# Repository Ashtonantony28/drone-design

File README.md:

# drone-design: NF-3D

A complete small quadcopter designed entirely in code, in a cloud container. It is built around the
[neuroflight-fc](https://github.com/Ashtonantony28/neuroflight-fc) learned flight controller and
flight-tested in that project's simulator.

- **Electronics:** the neuroflight-fc flight controller written in **Zener** with Diode's
  [`pcb`](https://github.com/diodeinc/pcb) toolchain (the E-CAD used in the Fable 5.2 electronics demo),
  laid out and DRC-checked in **KiCad 10**.
- **Mechanics:** a parametric frame in **build123d** (Python CAD), with mass, clearance, FEA and
  manufacturing exports.
- **Validation:** propulsion model, structural FEA and flight simulation, each with pass/fail gates.

## Gallery

**NF-3D Lite** (`lite/`, the low-cost brushed micro build): the 222-part detailed model that `lite/audit.py`
checks (0 overlaps, 0 floating parts), props turning in their real directions.

| Flight board as assembled | Carbon NF-3D v1 |
|:---:|:---:|
|  |  |

**Vision autonomy (simulation).** The AprilTag search, follow, approach and land behaviours flown closed-loop:
neuroflight-fc simulator, synthetic OV2640 frames, the laptop's real detector and controller, 150 ms link latency.
Nothing here has flown on hardware yet. Full 35 s clip with both episodes: [vision-replay.mp4](docs/media/vision-replay.mp4).

<sub>Regenerate: `xvfb-run -a python -m lite.turntable` (turntable, hero still, board still) and
`python -m lite.vision_replay` (needs `../neuroflight-fc`, torch, opencv).</sub>

## The vehicle

| | |
|---|---|
| Class | 3" ducted quad, 4S, sub-250 g |
| Motor spacing | 100 mm square (141 mm diagonal), widened from neuroflight's 92 mm so the 30.5 mm FC stack clears the ducts |
| All-up weight | **238.8 g** (CAD mass model, requirement ≤ 249 g) |
| Thrust/weight | **5.9** nominal, 4.3 in the pessimistic corner (requirement ≥ 3) |
| Hover | 28 % throttle, **8.8 min** hover (5.3 min pessimistic; requirement ≥ 4) |
| Frame | 3.0 mm carbon unibody with closed ring perimeter, PA12-CF printed ducts, TPU feet |
| FC | STM32H743, ICM-42688-P + BMI270, DPS310, 1 Gbit NAND, 36x36 mm 4-layer, 143 parts |

Every number comes from `spec/vehicle.yaml`. It is the single source that the CAD, mass model,
propulsion model, FEA and flight simulator all read.

## Verify

```
make verify          # mech -> propulsion -> fea -> flight (needs ../neuroflight-fc, torch)
cd ecad && python -m pytest check_design.py check_layout.py -q
docker run --rm -v $PWD:$PWD -w $PWD/ecad kicad/kicad:10.0.8 \
  kicad-cli pcb drc --severity-all boards/nf_fc/layout/nf_fc/nf_fc.kicad_pcb
```

| Check | Result |
|---|---|
| `mech.checks`: interference, clearances ≥ 1 mm, prop tip gap 1.0 mm, prop inside duct, feet are the lowest point, CoG offset | PASS |
| `prop.propulsion`, nominal and pessimistic corners (ct −15 %, cp +20 %, mass +5 %) | PASS |
| `mech.fea`: 20 g single-foot crash | SF **1.53** (≥ 1.5) at 1.6 mm mesh |
| `mech.fea`: full thrust | SF 31 |
| `mech.fea`: first frame mode | 213-221 Hz, 21-32 % away from hover rotor speed (≥ 20 %) |
| `flight.fly`: PID fallback on NF-3D vs the original neuroflight vehicle, 256 randomized vehicles per scenario | PASS (within 3 points in both corners) |
| `flight.fly`: v3 policy with thrust calibration (`v3cal`), same comparison (advisory) | within 3 points in both corners |
| `pcb build` (Zener) | 143 components, no errors or warnings |
| `ecad/check_design.py` (pin map, decoupling, rails, BOM vs neuroflight-fc) | 9 passed |
| `ecad/check_layout.py` (IMU spacing, DShot length, holes, decoupling, GND plane, USB pair, QSPI match, power widths and pours, track/space margin, silkscreen) | 17 passed |
| KiCad 10 DRC | **0 errors, 0 unconnected, 0 warnings** (the two library-footprint comparison checks, 120 warnings that depend on the installed footprint libraries, are set to ignore in `layout/place.py`) |

The frame took five FEA iterations to pass: crash safety factor 0.5 → 0.95 → 1.27 → 1.45 → 1.7, and
first mode 118 → 221 Hz. The changes were ring bridges, a 3 mm plate, wider arms, a bigger centre body
and filleted arm roots.

## Findings and open items

1. **The neural policy flies NF-3D after a thrust calibration, with no retraining.** neuroflight's
   `hover_ctbr_v3` used as-is holds up on the nominal NF-3D (99.2/85.9/95.3 % hover/tilt/throw). On the
   weak-motor corner it drops to 50/34/54 %, because its thrust command is in the reference vehicle's
   units and the policy has no integral action. `flight/fly.py` `CollectiveScaled` reads the command as
   mass-normalized and rescales it to this airframe:
   `a0' = (a0+1)·s − 1`, with `s = (T_max,ref · m) / (T_max · m_ref)`. That is what a hover-thrust
   estimator does on PX4/ArduPilot. With it, v3 scores **100/89.5/98.0 %** nominal and
   **100/90.2/98.0 %** pessimistic, against 100/90.6/97.3 % on the reference vehicle, so both corners
   are within the 3-point margin. Fine-tuning was tried first and doesn't work: every run lost v3's
   cm-level hover, including on the reference vehicle. `flight/retrain.py` records what was ruled out.
   Firmware follow-up for neuroflight-fc: apply `s` (or a learned hover thrust) between the policy
   output and the mixer.
2. **PCB before fab:** the layout items are done and asserted in `ecad/check_layout.py`
   (`python check_layout.py` prints the numbers). USB D+/D− is one 0.24 mm / 0.155 mm pair on L1
   (90.3 Ω by `ecad/layout/impedance.py`), 20.19 mm per line with 0.000 mm skew for both plug
   orientations (was D+ 53 mm vs D− 21 mm); 12.4 mm of it is coupled, the rest is fan-out at the
   MCU pins and the connector. The six QSPI lines are within 1.79 mm (was 29 mm apart on this
   routing), at the price of length: 53.6–55.4 mm each, because the longest line sets the target.
   VBAT, 5V and VBUS tracks are 0.25–0.5 mm (0.25 mm only in necks: 6 of 38 mm, 16 of 101 mm,
   2 of 28 mm) with L4 pours at the buck input and output; 3V3_D is the L3 pour. Silkscreen and
   the dangling via are clean. Still open: 342 mm of 1867 mm of track (18 %) stays 0.1 mm wide
   and 206 mm (11 %) has 0.1 mm space, in the MCU and FPGA escapes; 5V, VBUS and VBAT still have
   0.3–0.5 mm stretches on the 17.5 µm L3 (23, 9 and 9 mm) that should move to the outer layers;
   and the 90 Ω figure is a calculation, not a fab-controlled impedance. The router is this
   repo's own maze router (`ecad/layout/autoroute.py`); another seed or placement change can
   leave a net open, so re-run `layout/run.sh all` and the checks after any edit.
3. **Datasheet VERIFY items:** DPS310 / W25N01GV pinouts, LMR36015 variant and land pattern, IMU
   LGA-14 land patterns, crystal load capacitors, and the J2 pinout against the ESC you buy. All are
   marked `VERIFY` in `ecad/`.
4. **Propulsion numbers are estimates** until the M3 thrust stand; the pessimistic corner covers
   them. The arm mode is 21 % from the nominal hover rotor speed. Re-check once real hover rpm is known.

## Layout

```
spec/vehicle.yaml   single source of truth (geometry, parts, materials, motor/prop, requirements)
mech/               build123d frame, checks, FEA (gmsh + scikit-fem), exports -> out/cad/
prop/               battery-ESC-motor-prop model
flight/             flight validation and policy fine-tune in the neuroflight-fc simulator
ecad/               Zener FC design, layout scripts, KiCad board, checks, fab outputs (gerbers, PnP, STEP)
out/                generated reports, CAD exports, vehicle parameter sets
```

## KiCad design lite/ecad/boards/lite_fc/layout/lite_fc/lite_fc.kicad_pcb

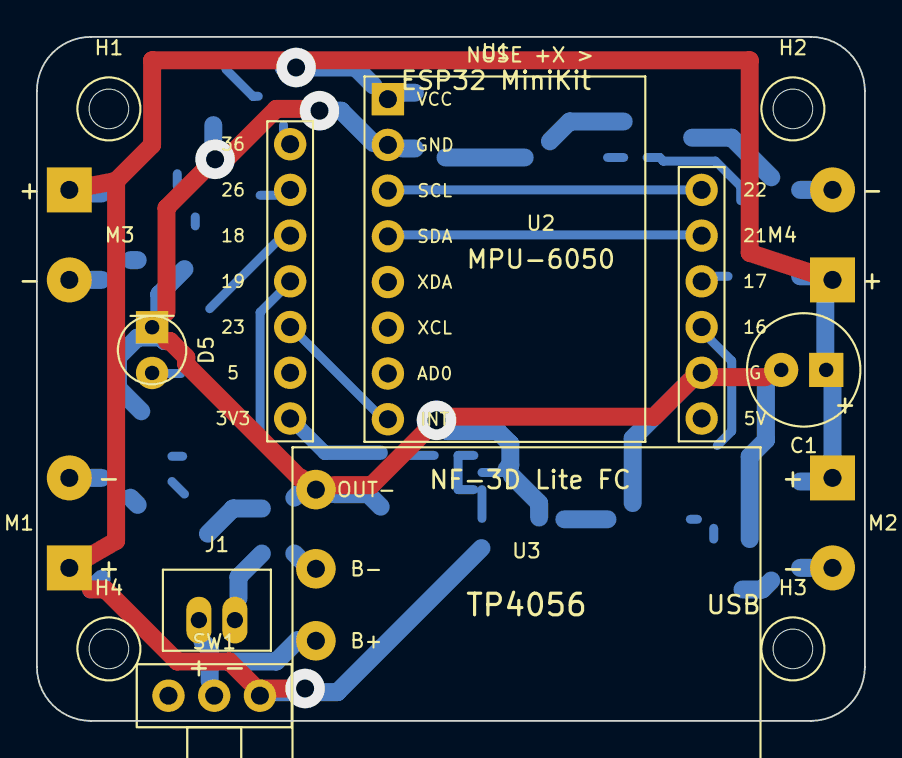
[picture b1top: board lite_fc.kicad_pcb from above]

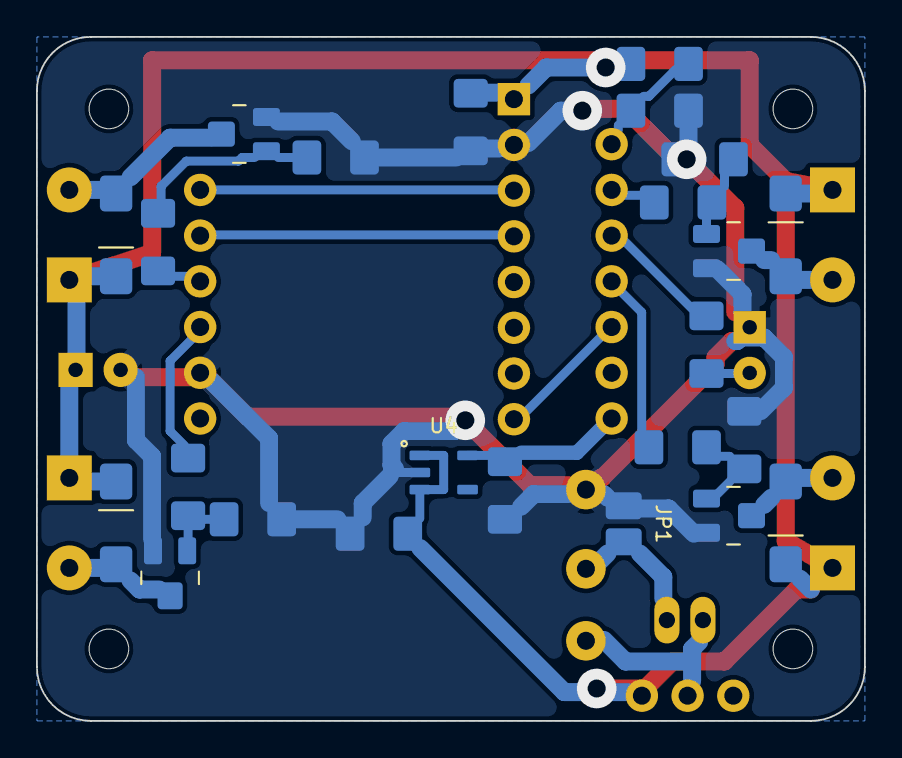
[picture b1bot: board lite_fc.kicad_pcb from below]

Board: 2 copper layers, 46.0 x 38.0 mm, 39 parts (24 on the bottom side), 23 nets.

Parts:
C1: 470uF 6.3V electrolytic D6.3; CP_Radial_D6.3_P2.5_Mill
C2, C3: 10uF 10V X5R 1206; C_1206_Mill
C4: 100nF 50V X7R 1206; C_1206_Mill
D1, D2, D3, D4: B5819W Schottky 1A 40V SOD-123; D_SMA_SOD-123_Mill
D5: 3mm LED; LED_D3.0_Mill
H1, H2, H3, H4: MountingHole; MountingHole_2.2mm_M2_Mill
J1: JST PH2.0 2-pin vertical (battery); JST_PH_B2B_Vertical_Mill
JP1: protection bypass (open); SolderJumper_2_Open_Mill
M1, M2, M3, M4: 8520 brushed motor pads; MotorPads_2_P5.0_Mill
Q1, Q2, Q3, Q4: AO3400A; SOT-23_Mill
R1, R2, R3, R4: 100R 1% 1206; R_1206_Mill
R5, R6, R7, R8: 10k 1% 1206; R_1206_Mill
R9: 100k 1% 1206; R_1206_Mill
R10: 47k 1% 1206; R_1206_Mill
R11: 330R 1% 1206; R_1206_Mill
SW1: SS-12D00 SPDT slide switch; SW_SPDT_SS12D00_Mill
U1: ESP32 MiniKit (MH-ET LIVE D1 mini, ESP32-WROOM-32); ESP32_MiniKit_InnerRows_Mill
U2: GY-521 MPU-6050; GY521_MPU6050_Mill
U3: TP4056 + DW01 charger module (03962A); TP4056_Protected_Module_Mill
U4: ME6211C33M5G 3.3V 500mA LDO; SOT-23-5_Mill

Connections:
3V3: C3.1, U1.L8, U4.5
BAT_N: J1.1, JP1.2, U3.2
BAT_P: J1.2, SW1.2, U3.1
GND: C1.2, C2.2, C3.2, C4.2, D5.1, JP1.1, Q1.2, Q2.2, Q3.2, Q4.2, R5.2, R6.2, R7.2, R8.2, R10.2, U1.R7, U2.2, U3.3, U4.2
I2C_SCL: U1.R3, U2.3
I2C_SDA: U1.R4, U2.4
IMU_INT: U1.L6, U2.8
LED: R11.1, U1.L4
LED_A: D5.2, R11.2
M1_G: Q1.1, R1.2, R5.1
M1_N: D1.2, M1.2, Q1.3
M1_PWM: R1.1, U1.L5
M2_G: Q2.1, R2.2, R6.1
M2_N: D2.2, M2.2, Q2.3
M2_PWM: R2.1, U1.R6
M3_G: Q3.1, R3.2, R7.1
M3_N: D3.2, M3.2, Q3.3
M3_PWM: R3.1, U1.L3
M4_G: Q4.1, R4.2, R8.1
M4_N: D4.2, M4.2, Q4.3
M4_PWM: R4.1, U1.R5
VBAT: C1.1, C2.1, C4.1, D1.1, D2.1, D3.1, D4.1, M1.1, M2.1, M3.1, M4.1, R9.1, SW1.3, U2.1, U4.1, U4.3
VBAT_SENSE: R9.2, R10.1, U1.L2

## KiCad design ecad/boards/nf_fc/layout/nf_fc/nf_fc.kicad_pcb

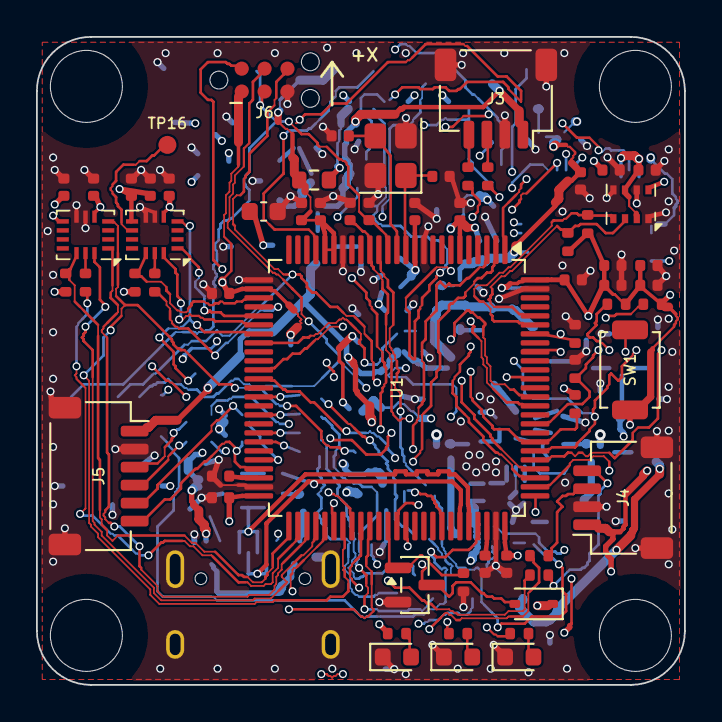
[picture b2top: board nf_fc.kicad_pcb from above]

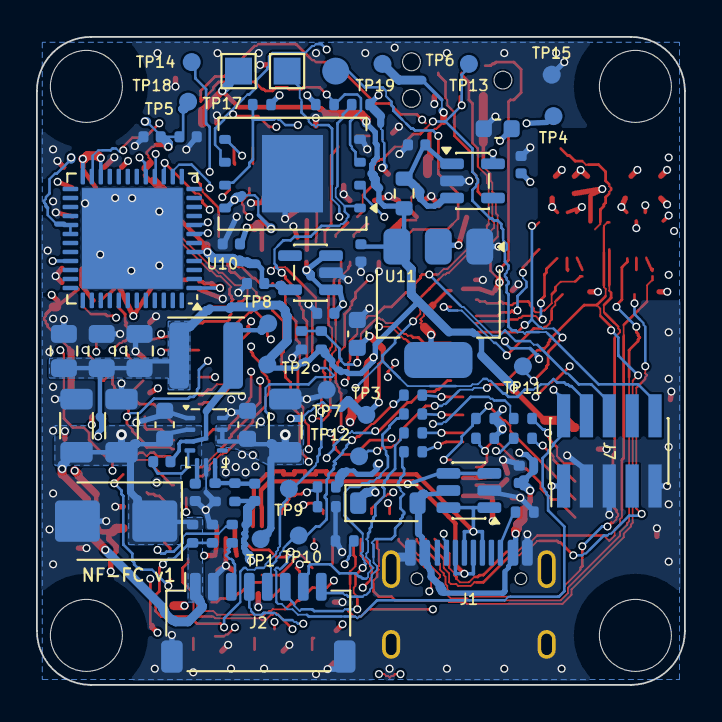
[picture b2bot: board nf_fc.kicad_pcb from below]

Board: 4 copper layers, 36.0 x 36.0 mm, 143 parts (76 on the bottom side), 90 nets.

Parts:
C1, C2, C3, C4, C5, C6, C7, C8, C9, C10, C11, C14, C15, C16, C19, C20, C24, C25, C26, C27, C28, C29, C34, C49: 100nF 16V X7R; C_0402_1005Metric
C12: 10nF 50V X7R; C_0402_1005Metric
C13, C21, C22: 2.2uF 6.3V X5R; C_0402_1005Metric
C17, C18: 12pF 50V C0G; C_0402_1005Metric
C23, C36, C38, C39, C41, C42, C46: 1uF 25V X5R; C_0402_1005Metric
C30, C37, C40: 10uF 10V X5R; C_0603_1608Metric
C31, C32, C33: 22uF 25V X5R; C_0805_2012Metric
C35: 20pF 50V C0G; C_0402_1005Metric
C43, C44, C45: 2.2uF 50V X7R; C_1206_3216Metric
C47, C48: 220nF 100V X7R; C_0603_1608Metric
D1: B5819W; D_SOD-123
D2: 1N4148WS; D_SOD-323
D3: 26V TVS Diode; D_SMB
D4: LED GREEN 2.7–3.2V (3V nom.); LED_0603_1608Metric
D5: LED BLUE 2.7–3.2V (3V nom.); LED_0603_1608Metric
D6: LED RED 2V 10%; LED_0603_1608Metric
FB1, FB2: 600 1A 100MHz; R_0603_1608Metric
H1, H2, H3, H4: MountingHole; MountingHole_4.0mm_M3_Grommet
J1: TYPE-C-31-M-12; USB_C_Receptacle_HRO_TYPE-C-31-M-12
J2: SM08B-SRSS-TB(LF)(SN); JST_SH_SM08B-SRSS-TB_1x08-1MP_P1.00mm_Horizontal
J3, J4: SM04B-SRSS-TB(LF)(SN); JST_SH_SM04B-SRSS-TB_1x04-1MP_P1.00mm_Horizontal
J5: SM06B-SRSS-TB(LF)(SN); JST_SH_SM06B-SRSS-TB_1x06-1MP_P1.00mm_Horizontal
J6: Conn_ARM_SWD_TagConnect_TC2030-NL; Tag-Connect_TC2030-IDC-NL_2x03_P1.27mm_Vertical
J7: FTSH-105-01-F-DV-K; PinHeader_2x05_P1.27mm_Vertical_SMD
L1: 6.8uH; L_Sunlord_SWPA4030S
Q1: AO3400A; SOT-23
R1, R2: 4.7k 1%; R_0402_1005Metric
R3, R6, R9, R10, R15, R16: 100 1%; R_0402_1005Metric
R4, R5: 2.2k 1%; R_0402_1005Metric
R7, R8: 5.1k 1%; R_0402_1005Metric
R11, R12, R13, R14: 33 1%; R_0402_1005Metric
R17, R18, R19, R20, R22, R24, R25, R26, R28, R31, R32, R35, R37, R38: 10k 1%; R_0402_1005Metric
R21, R23: 0; R_0402_1005Metric
R27, R30: 100k 1%; R_0402_1005Metric
R29: 24.9k 1%; R_0402_1005Metric
R33, R34, R39, R40, R41: 1k 1%; R_0402_1005Metric
R36: 20k 1%; R_0402_1005Metric
SW1: TS-1088-AR02016; SW_SPST_TS-1088-xR020
TP1, TP2, TP3, TP4, TP5, TP6, TP7, TP8, TP9, TP10, TP11, TP12, TP13, TP14, TP15, TP16: TestPoint_Small; TestPoint_Pad_D1.0mm
TP17, TP18: TestPoint_Small; TestPoint_Pad_1.5x1.5mm
TP19: TestPoint_Small; TestPoint_Pad_D1.5mm
U1: STM32H743VIT6; LQFP-100_14x14mm_P0.5mm
U2: ICM-42688-P; Bosch_LGA-14_3x2.5mm_P0.5mm
U3: BMI270; Bosch_LGA-14_3x2.5mm_P0.5mm
U4: DPS310XTSA1; Bosch_LGA-8_2x2.5mm_P0.65mm_ClockwisePinNumbering
U5: W25N01GVZEIG; WSON-8-1EP_8x6mm_P1.27mm_EP3.4x4.3mm
U6: LMR36015FBRNXR; Texas_RNX0012C_VQFN-14-11-1EP_2x3mm_P0.5mm_EP0.25x1.825mm
U7: LDL1117S33R; SOT-223-3_TabPin2
U8: LP5907MFX-3.3/NOPB; SOT-23-5
U9: USBLC6-2SC6; SOT-23-6
U10: iCE40UP5K-SG48ITR; QFN-48-1EP_7x7mm_P0.5mm_EP5.6x5.6mm
U11: TLV75512PDBVR; SOT-23-5
Y1: 8MHz; Crystal_SMD_3225-4Pin_3.2x2.5mm

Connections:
1V2_FPGA: C8.1, C9.1, C10.1, C42.1, TP5.1, U10.5, U10.29, U10.30, U11.5
3V3_D: C1.1, C2.1, C4.1, C5.1, C6.1, C7.1, C11.1, C20.1, C25.1, C26.1, C27.1, C28.1, C29.1, C30.1, C37.1, C41.1, FB2.1, J6.1, J7.1, R1.2, R2.2, R4.2, R5.2, R17.2, R18.2, R19.2, R25.2, R26.2, R28.2, R39.1, SW1.1, TP3.1, U1.6, U1.11, U1.27, U1.50, U1.75, U1.100, U4.2, U4.6, U4.8, U5.8, U7.2, U10.1, U10.22, U10.24, U10.33, U11.1, U11.3
3V3_IMU: C12.1, C13.1, C14.1, C15.1, C16.1, C39.1, C40.1, R20.2, R22.2, TP4.1, U2.5, U2.8, U3.5, U3.8, U8.5
5V: C31.1, C32.1, C33.1, C35.1, C36.1, D1.1, D2.1, FB1.1, J3.1, J4.1, J5.1, L1.2, R30.1, R32.1, TP2.1, TP18.1, U7.3
5V_SENSE: R31.1, R32.2, U1.33
AUX_RX: R3.1, U1.64
AUX_SCL: J5.5, R4.1, U1.46
AUX_SDA: J5.6, R5.1, U1.47
AUX_TX: R6.1, U1.63
BARO_SCL: R1.1, U1.95, U4.4
BARO_SDA: R2.1, U1.96, U4.3
BEEPER: Q1.1, R38.1, U1.62
BOOT0: R24.1, SW1.2, TP14.1, U1.94
CONN.AUX_RX_CONN: J5.4, R3.2
CONN.AUX_TX_CONN: J5.3, R6.2
CONN.ESC_M2: J2.6, R12.2
CONN.ESC_M3: J2.7, R13.2
CONN.ESC_M4: J2.8, R14.2
CONN.FLOW_RX_CONN: J4.4, R9.2
CONN.FLOW_TX_CONN: J4.3, R10.2
CONN.RC_RX_CONN: J3.4, R15.2
CONN.RC_TX_CONN: J3.3, R16.2
CONN.USB_CC1: J1.A5, R7.1
CONN.USB_CC2: J1.B5, R8.1
CURR_SENSE: C49.1, R33.2, U1.16
ESC_CUR: J2.3, R33.1
ESC_M1: J2.5, R11.2, TP10.1
ESC_TLM: J2.4, U1.37
FLOW_RX: R9.1, U1.56
FLOW_TX: R10.1, U1.55
FPGA_CDONE: R25.1, U1.82, U10.7
FPGA_CRESET_B: R26.1, U1.81, U10.8
FPGA_IRQ: R27.1, U1.84, U10.23
FPGA_MISO: U1.79, U10.14
FPGA_MOSI: U1.80, U10.17
FPGA_SCK: U1.78, U10.15
FPGA_SS_B: R28.1, U1.77, U10.16
GND: C1.2, C2.2, C3.2, C4.2, C5.2, C6.2, C7.2, C8.2, C9.2, C10.2, C11.2, C12.2, C13.2, C14.2, C15.2, C16.2, C17.2, C18.2, C19.2, C20.2, C21.2, C22.2, C23.2, C24.2, C25.2, C26.2, C27.2, C28.2, C29.2, C30.2, C31.2, C32.2, C33.2, C36.2, C37.2, C38.2, C39.2, C40.2, C41.2, C42.2, C43.2, C44.2, C45.2, C46.2, C47.2, C48.2, C49.2, D3.2, D4.1, D5.1, D6.1, J1.A1, J1.A12, J1.B1, J1.B12, J1.SH, J2.2, J2.MP, J3.2, J3.MP, J4.2, J4.MP, J5.2, J5.MP, J6.5, J7.3, J7.5, J7.9, Q1.2, R7.2, R8.2, R24.2, R27.2, R29.2, R31.2, R34.2, R36.2, R38.2, TP7.1, TP15.1, U1.10, U1.19, U1.26, U1.49, U1.74, U1.99, U2.6, U2.7, U3.6, U3.7, U4.1, U4.5, U4.7, U5.4, U5.9, U6.1, U6.6, U6.11, U7.1, U8.2, U9.2, U10.49, U11.2, Y1.2, Y1.4
IMU.IMUA_CLKIN: TP16.1, U2.9
IMU.IMUA_SCK_R: R21.2, U2.13
IMU.IMUB_SCK_R: R23.2, U3.13
IMUA_CS: R20.1, U1.28, U2.12
IMUA_INT1: TP11.1, U1.32, U2.4
IMUA_MISO: U1.30, U2.1
IMUA_MOSI: U1.31, U2.14
IMUA_SCK: R21.1, U1.29
IMUB_CS: R22.1, U1.51, U3.12
IMUB_INT1: TP12.1, U1.57, U3.4
IMUB_MISO: U1.53, U3.1
IMUB_MOSI: U1.54, U3.14
IMUB_SCK: R23.1, U1.52
LED0: R40.1, U1.2
LED1: R41.1, U1.3
LED_STRIP: TP19.1, U1.22
MCU.HSE_IN: C17.1, U1.12, Y1.1
MCU.HSE_OUT: C18.1, U1.13, Y1.3
MCU.VCAP_1: C21.1, U1.48
MCU.VCAP_2: C22.1, U1.73
MOTOR0: R11.1, U1.39
MOTOR1: R12.1, U1.41
MOTOR2: R13.1, U1.43
MOTOR3: R14.1, U1.44
NRST: C19.1, J6.3, J7.10, TP13.1, U1.14
PWR.BUCK_BOOT: C34.1, U6.4
PWR.BUCK_FB: C35.2, R29.1, R30.2, U6.7
PWR.BUCK_SW: C34.2, L1.1, TP8.1, U6.3, U6.12
PWR.BUCK_VCC: C46.1, U6.5
PWR.IMU_LDO_IN: C38.1, FB1.2, U8.1, U8.3
QSPI_CLK: U1.36, U5.6
QSPI_IO0: U1.58, U5.5
QSPI_IO1: U1.59, U5.2
QSPI_IO2: R17.1, U1.1, U5.3
QSPI_IO3: R18.1, U1.60, U5.7
QSPI_NCS: R19.1, U1.92, U5.1
RX_RX: R15.1, U1.87
RX_TX: R16.1, U1.86
SWCLK: J6.4, J7.4, U1.76
SWDIO: J6.2, J7.2, U1.72
SWO: J6.6, J7.6, U1.89
UI.BUZZER_N: D2.2, Q1.3, TP17.1
UI.LED_PWR_A: D4.2, R39.2
UI.LED_STATUS_A: D5.2, R40.2
UI.LED_WARN_A: D6.2, R41.2
USB_N: J1.A7, J1.B7, U1.70, U9.3, U9.4
USB_P: J1.A6, J1.B6, U1.71, U9.1, U9.6
VBAT: C43.1, C44.1, C45.1, C47.1, C48.1, D3.1, J2.1, R35.1, TP1.1, U6.2, U6.9, U6.10
VBAT_SENSE: R34.1, R35.2, TP9.1, U1.15
VBUS: C3.1, D1.2, J1.A4, J1.A9, J1.B4, J1.B9, R37.1, U9.5
VBUS_SENSE: R36.1, R37.2, U1.68
VDDA: C23.1, C24.1, FB2.2, TP6.1, U1.20, U1.21

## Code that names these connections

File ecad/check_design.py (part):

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    "J4": {"1": "5V", "2": "GND", "3": "CONN.FLOW_TX_CONN", "4": "CONN.FLOW_RX_CONN"},
    "J5": {"1": "5V", "2": "GND", "3": "CONN.AUX_TX_CONN", "4": "CONN.AUX_RX_CONN", "5": "AUX_SCL", "6": "AUX_SDA"},
    "J6": {"1": "3V3_D", "2": "SWDIO", "3": "NRST", "4": "SWCLK", "5": "GND", "6": "SWO"},
    # ARM Cortex-Debug 10-pin: 1 VTref, 2 SWDIO, 3/5/9 GND, 4 SWCLK, 6 SWO, 10 nRESET
    "J7": {"1": "3V3_D", "2": "SWDIO", "3": "GND", "4": "SWCLK", "5": "GND", "6": "SWO", "9": "GND", "10": "NRST"},
}
# Series element between an MCU-side net and a connector-side net: (net a, net b, value)
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

def test_connectors_and_series():
    """DESIGN.md section 6 pinouts; INTERFACES.md section 2 motor order (MOTOR0-3 -> ESC M1-M4)."""
    _, comps = netlist()
    for ref, pads in CONNECTORS.items():
        for pad, net in pads.items():
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        assert len(nets["MOTOR%d" % i]["ports"]) == 2
    # USB: both data lines pass the ESD part, CC pins have Rd
    j1, u9, mcu = comps["J1"], comps["U9"], comps["U1"]
    assert j1.pins["D+"] == u9.pins["I/O1"] == mcu.pins["PA12"] == "USB_P"
    assert j1.pins["D-"] == u9.pins["I/O2"] == mcu.pins["PA11"] == "USB_N"
    for cc in ("CC1", "CC2"):
        r = two_pin("resistor", j1.pins[cc], "GND")
        assert len(r) == 1 and value_is(r[0], "5.1k")
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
